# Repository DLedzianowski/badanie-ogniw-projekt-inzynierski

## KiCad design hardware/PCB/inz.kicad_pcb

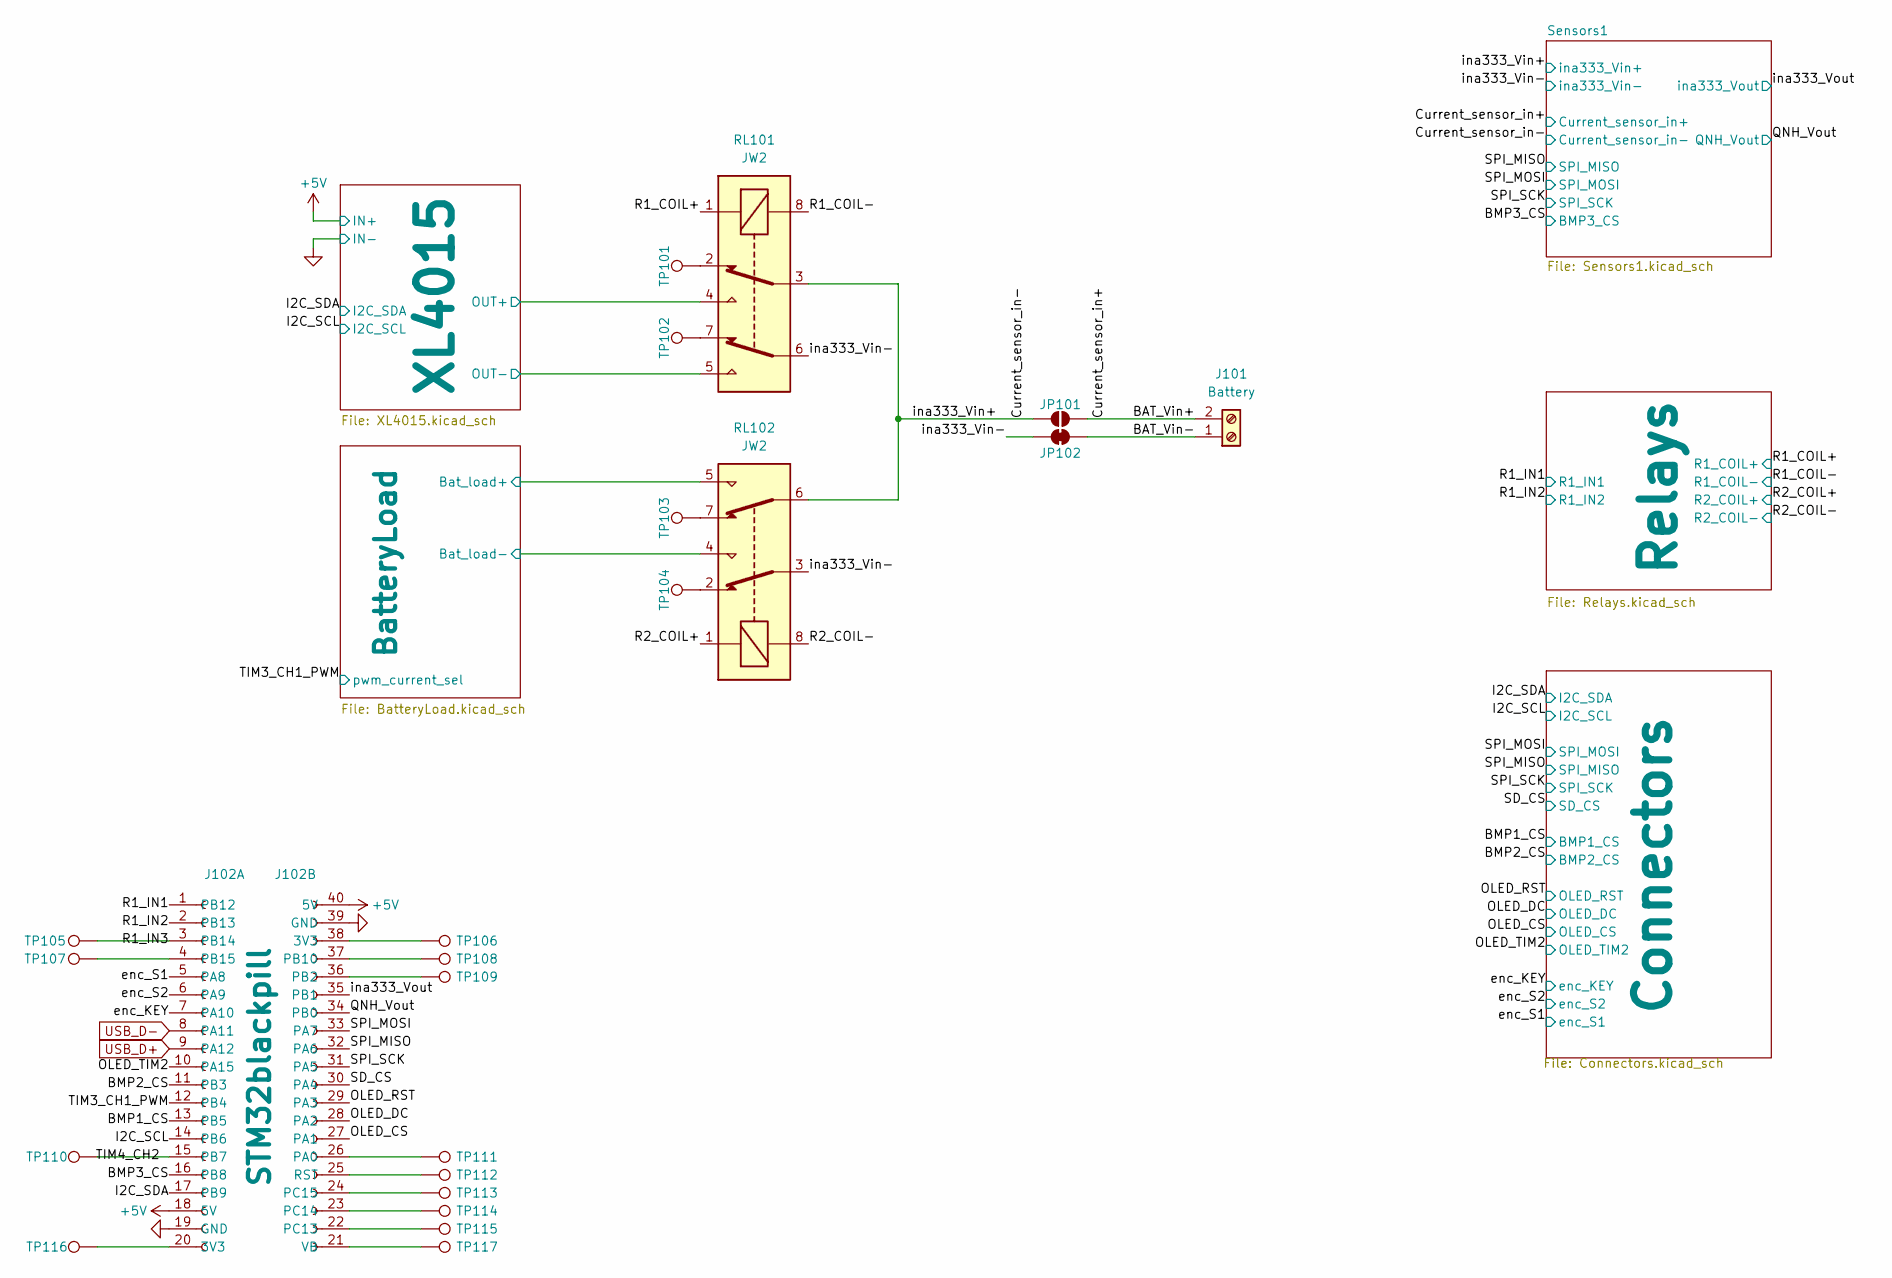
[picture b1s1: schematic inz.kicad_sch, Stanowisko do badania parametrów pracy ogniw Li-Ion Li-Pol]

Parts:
J101: Battery; TerminalBlock_Phoenix_MKDS-1,5-2_1x02_P5.00mm_Horizontal
J102: STM32blackpill; MFR Part ICSockets-40P; JLCPCB Part C2332
JP101: SolderJumper_2_Open; SolderJumper-2_P1.3mm_Open_TrianglePad1.0x1.5mm
JP102: Jumper_2_Bridged; PinHeader_1x02_P2.54mm_Vertical
RL101, RL102: JW2; Relay_DPDT_Panasonic_JW2; MFR Part JW2SN-DC5V
TP101, TP102, TP103, TP104, TP105, TP106, TP107, TP108, TP109, TP110, TP111, TP112, TP113, TP114, TP115, TP116, TP117: TestPoint; TestPoint_THTPad_D1.5mm_Drill0.7mm

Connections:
+5V: J102.18 (5V), J102.40 (5V), RL101.1, RL102.1; also elsewhere on the board
/BAT_Vin+: J101.2, JP101.1 (A); also elsewhere on the board
/BAT_Vin-: J101.1, JP102.2 (B)
/BMP1_CS: J102.13 (PB5); also elsewhere on the board
/BMP2_CS: J102.11 (PB3); also elsewhere on the board
/BMP3_CS: J102.16 (PB8); also elsewhere on the board
/BatteryLoad/Bat_load+: RL102.5; also elsewhere on the board
/Current_sensor_in-: JP101.2 (B), RL101.3, RL102.6; also elsewhere on the board
/I2C_SCL: J102.14 (PB6); also elsewhere on the board
/I2C_SDA: J102.17 (PB9); also elsewhere on the board
/OLED_CS: J102.27 (PA1); also elsewhere on the board
/OLED_DC: J102.28 (PA2); also elsewhere on the board
/OLED_RST: J102.29 (PA3); also elsewhere on the board
/OLED_TIM2: J102.10 (PA15); also elsewhere on the board
/QNH_Vout: J102.34 (PB0); also elsewhere on the board
/R1_COIL-: RL101.8; also elsewhere on the board
/R1_IN1: J102.1 (PB12); also elsewhere on the board
/R1_IN2: J102.2 (PB13); also elsewhere on the board
/R1_IN3: J102.3 (PB14), TP105.1
/R2_COIL-: RL102.8; also elsewhere on the board
/SD_CS: J102.30 (PA4); also elsewhere on the board
/SPI_MISO: J102.32 (PA6); also elsewhere on the board
/SPI_MOSI: J102.33 (PA7); also elsewhere on the board
/SPI_SCK: J102.31 (PA5); also elsewhere on the board
/TIM3_CH1_PWM: J102.12 (PB4); also elsewhere on the board
/TIM4_CH2: J102.15 (PB7), TP110.1
/XL4015/OUT+: RL101.4; also elsewhere on the board
/XL4015/OUT-: RL101.5; also elsewhere on the board
/enc_KEY: J102.7 (PA10); also elsewhere on the board
/enc_S1: J102.5 (PA8); also elsewhere on the board
/enc_S2: J102.6 (PA9); also elsewhere on the board
/ina333_Vin-: JP102.1 (A), RL101.6, RL102.3; also elsewhere on the board
/ina333_Vout: J102.35 (PB1); also elsewhere on the board
GND: J102.19 (GND), J102.39 (GND), RL102.4; also elsewhere on the board
unnamed: J102.20 (3V3), TP116.1
unnamed: J102.4 (PB15), TP107.1
unnamed: J102.38 (3V3), TP106.1
unnamed: J102.26 (PA0), TP111.1
unnamed: J102.36 (PB2), TP109.1
unnamed: J102.37 (PB10), TP108.1
unnamed: J102.22 (PC13), TP115.1
unnamed: J102.23 (PC14), TP114.1
unnamed: J102.24 (PC15), TP113.1
unnamed: J102.25 (RST), TP112.1
unnamed: J102.21 (VB), TP117.1
unnamed: RL101.2, TP101.1
unnamed: RL101.7, TP102.1
unnamed: RL102.2, TP104.1
unnamed: RL102.7, TP103.1
USB_D+: J102.9 (PA12); also elsewhere on the board
USB_D-: J102.8 (PA11); also elsewhere on the board

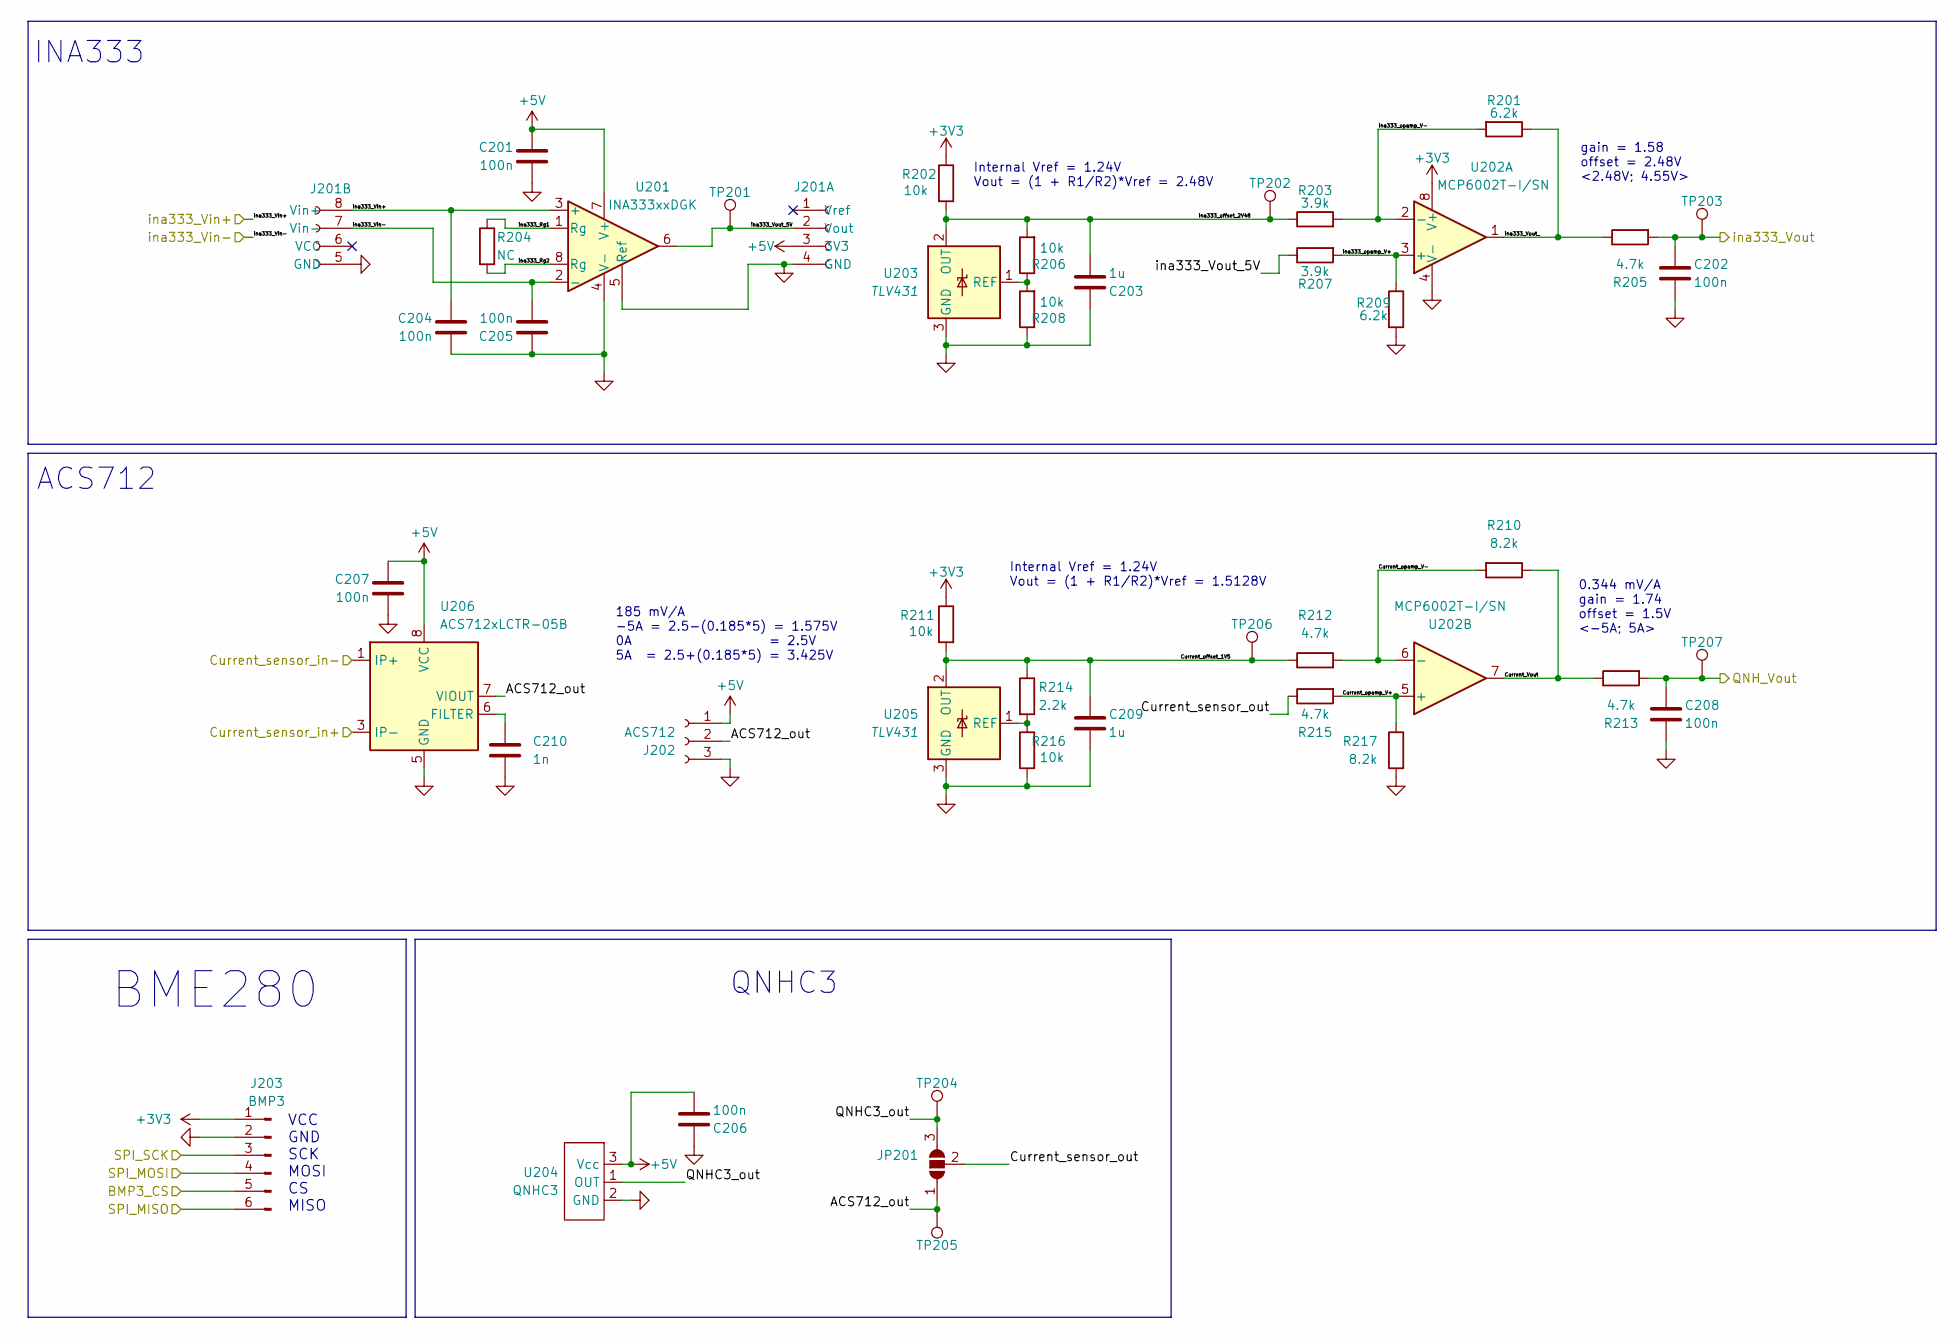
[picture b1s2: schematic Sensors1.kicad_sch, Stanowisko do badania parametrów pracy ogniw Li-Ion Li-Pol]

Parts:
C201, C202, C204, C205, C206, C207, C208: 100n; C_0805_2012Metric; MFR Part CL21B104KCFNNNE; JLCPCB Part C28233
C203, C209: 1u; C_0805_2012Metric; MFR Part CL21B105KBFNNNE; JLCPCB Part C28323
C210: 1n; C_0805_2012Metric; MFR Part CL21B102KBCNNNC; JLCPCB Part C46653
J201: ina333; board_ina333
J202: ACS712; PinHeader_1x03_P2.54mm_Vertical
J203: BMP3; PinHeader_1x06_P2.54mm_Vertical
JP201: SolderJumper_3_Open; SolderJumper-3_P2.0mm_Open_TrianglePad1.0x1.5mm_NumberLabels
R201, R209: 6.2k; R_0805_2012Metric; MFR Part 0805W8F6201T5E; JLCPCB Part C17767
R202, R206, R208, R211, R216: 10k; R_0805_2012Metric; MFR Part 0805W8F1002T5E; JLCPCB Part C17414
R203, R207: 3.9k; R_0805_2012Metric; MFR Part 0805W8F3901T5E; JLCPCB Part C17614
R204: NC; R_0805_2012Metric
R205, R212, R213, R215: 4.7k; R_0805_2012Metric; MFR Part 0805W8F4701T5E; JLCPCB Part C17673
R210, R217: 8.2k; R_0805_2012Metric; MFR Part 0805W8F8201T5E; JLCPCB Part C17828
R214: 2.2k; R_0805_2012Metric; MFR Part 0805W8F2201T5E; JLCPCB Part C17520
TP201, TP202, TP203, TP204, TP205, TP206, TP207: TestPoint; TestPoint_THTPad_D1.5mm_Drill0.7mm
U201: INA333xxDGK; VSSOP-8_3x3mm_P0.65mm; MFR Part INA333AIDGKT; JLCPCB Part C2057648
U202: MCP6002T-I/SN; SOIC-8_3.9x4.9mm_P1.27mm; MFR Part MCP6002T-I/SN; JLCPCB Part C7377
U203, U205: TLV431; SOT-23; MFR Part TLV431AIDBZR; JLCPCB Part C56765
U204: QNHC3
U206: ACS712xLCTR-05B; SOIC-8_3.9x4.9mm_P1.27mm; MFR Part ACS712ELCTR-05B-T; JLCPCB Part C44471

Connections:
+3V3: J203.1, R202.1, R211.1, U202.8 (V+); also elsewhere on the board
+5V: C201.1, C206.2, C207.1, J201.3 (3V3), J202.1, U201.7 (V+), U204.3 (Vcc), U206.8 (VCC); also elsewhere on the board
/BAT_Vin+: U206.3 (IP-), U206.4 (IP-); also elsewhere on the board
/BMP3_CS: J203.5; also elsewhere on the board
/Current_sensor_in-: C204.1, J201.8 (Vin+), U201.3 (+), U206.1 (IP+), U206.2 (IP+); also elsewhere on the board
/QNH_Vout: C208.1, R213.2, TP207.1; also elsewhere on the board
/SPI_MISO: J203.6; also elsewhere on the board
/SPI_MOSI: J203.4; also elsewhere on the board
/SPI_SCK: J203.3; also elsewhere on the board
/Sensors1/ACS712_out: J202.2, JP201.1 (A), TP205.1, U206.7 (VIOUT)
/Sensors1/Current_Vout: R210.1, R213.1, U202.7
/Sensors1/Current_offset_1V5: C209.1, R211.2, R212.1, R214.1, TP206.1, U205.2 (OUT)
/Sensors1/Current_opamp_V+: R215.2, R217.1, U202.5 (+)
/Sensors1/Current_opamp_V-: R210.2, R212.2, U202.6 (-)
/Sensors1/Current_sensor_out: JP201.2 (C), R215.1
/Sensors1/QNHC3_out: JP201.3 (B), TP204.1, U204.1 (OUT)
/Sensors1/ina333_Rg1: R204.1, U201.1 (Rg)
/Sensors1/ina333_Rg2: R204.2, U201.8 (Rg)
/Sensors1/ina333_Vout_: R201.1, R205.1, U202.1
/Sensors1/ina333_Vout_5V: J201.2 (Vout), R207.1, TP201.1, U201.6
/Sensors1/ina333_offset_2V48: C203.2, R202.2, R203.1, R206.2, TP202.1, U203.2 (OUT)
/Sensors1/ina333_opamp_V+: R207.2, R209.1, U202.3 (+)
/Sensors1/ina333_opamp_V-: R201.2, R203.2, U202.2 (-)
/ina333_Vin-: C205.2, J201.7 (Vin-), U201.2 (-); also elsewhere on the board
/ina333_Vout: C202.1, R205.2, TP203.1; also elsewhere on the board
GND: C201.2, C202.2, C203.1, C204.2, C205.1, C206.1, C207.2, C208.2, C209.2, C210.2, J201.4 (GND), J201.5 (GND), J202.3, J203.2, R208.1, R209.2, R216.2, R217.2, U201.4 (V-), U201.5 (Ref), U202.4 (V-), U203.3 (GND), U204.2 (GND), U205.3 (GND), U206.5 (GND); also elsewhere on the board
unnamed: R206.1, R208.2, U203.1 (REF)
unnamed: R214.2, R216.1, U205.1 (REF)
unnamed: C210.1, U206.6 (FILTER)

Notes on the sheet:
BME280
185 mV/A -5A = 2.5-(0.185*5) = 1.575V 0A = 2.5V 5A = 2.5+(0.185*5) = 3.425V
Internal Vref = 1.24V Vout = (1 + R1/R2)*Vref = 2.48V
gain = 1.58 offset = 2.48V <2.48V; 4.55V>
VCC GND SCK MOSI CS MISO
QNHC3
INA333
ACS712
Internal Vref = 1.24V Vout = (1 + R1/R2)*Vref = 1.5128V
0.344 mV/A gain = 1.74 offset = 1.5V <-5A; 5A>

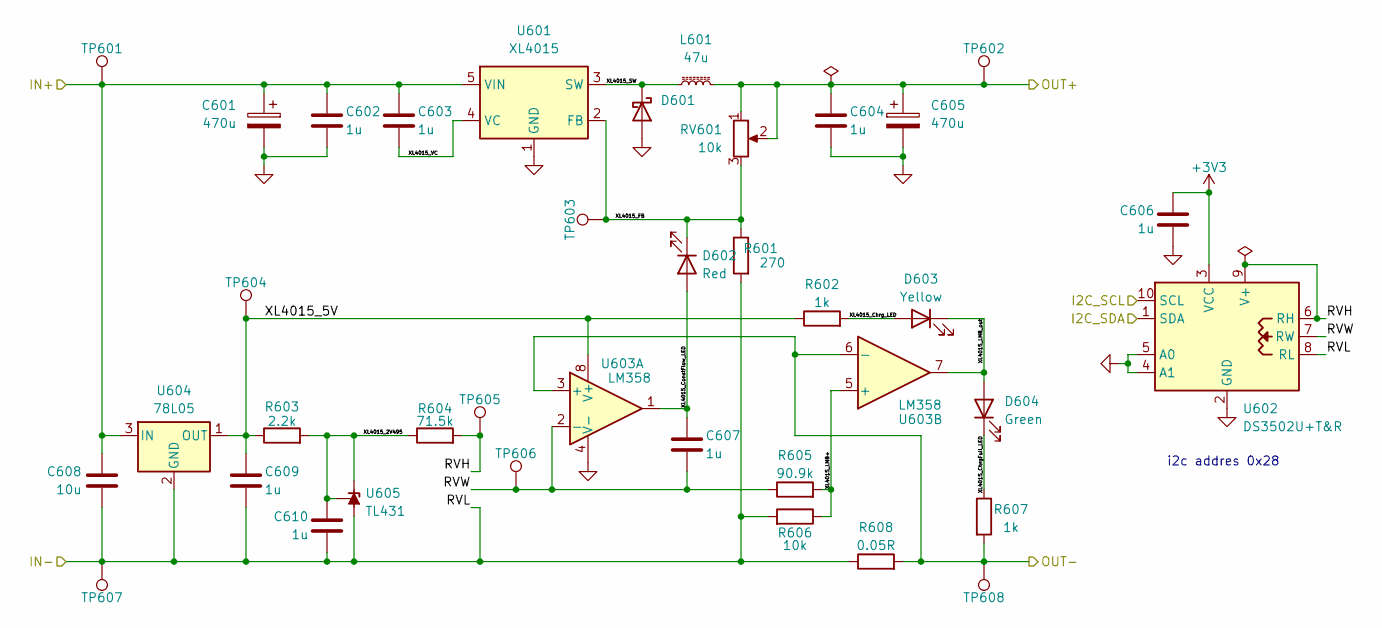
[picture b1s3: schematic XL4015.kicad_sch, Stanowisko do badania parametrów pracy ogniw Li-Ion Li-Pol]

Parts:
C601, C605: 470u; C_Elec_10x10.2; MFR Part RVT1E471M1010; JLCPCB Part C3351
C602, C603, C604, C606, C607, C609, C610: 1u; C_0805_2012Metric; MFR Part CL21B105KBFNNNE; JLCPCB Part C28323
C608: 10u; C_1206_3216Metric; MFR Part CL31A106KOHNNNE; JLCPCB Part C1849
D601: MBRD1045; D_SMA; MFR Part C22452; JLCPCB Part C22452
D602: Red; LED_0805_2012Metric; MFR Part NCD0805R1; JLCPCB Part C84256
D603: Yellow; LED_0805_2012Metric; MFR Part KT-0805Y; JLCPCB Part C2296
D604: Green; LED_0805_2012Metric; MFR Part KT-0805G; JLCPCB Part C2297
L601: 47u; L_Toroid_Vertical_L16.0mm_W8.0mm_P7.62mm; MFR Part XR050125TS470MVL8; JLCPCB Part C18213949
R601: 270; R_0805_2012Metric; MFR Part 0805W8F2700T5E; JLCPCB Part C17590
R602, R607: 1k; R_0805_2012Metric; MFR Part 0805W8F1001T5E; JLCPCB Part C17513
R603: 2.2k; R_0805_2012Metric; MFR Part 0805W8F2201T5E; JLCPCB Part C17520
R604: 71.5k; R_0805_2012Metric; MFR Part 0805W8F7152T5E; JLCPCB Part C17811
R605: 90.9k; R_0805_2012Metric; MFR Part 0805W8F9092T5E; JLCPCB Part C17860
R606: 10k; R_0805_2012Metric; MFR Part 0805W8F1002T5E; JLCPCB Part C17414
R608: 0.05R; R_2512_6332Metric; MFR Part 25121WF500MT4E; JLCPCB Part C127698
RV601: 10k; Potentiometer_Bourns_3299W_Vertical
TP601, TP602, TP603, TP604, TP605, TP606, TP607, TP608: TestPoint; TestPoint_THTPad_D1.5mm_Drill0.7mm
U601: XL4015; TO-263-5_TabPin3; MFR Part XL4015E1; JLCPCB Part C51661
U602: DS3502U+T&R; TSSOP-10_3x3mm_P0.5mm; MFR Part DS3502U+T&R; JLCPCB Part C2649363
U603: LM358; SOIC-8_3.9x4.9mm_P1.27mm; MFR Part LM358DR2G; JLCPCB Part C7950
U604: 78L05; SOT-89-3; MFR Part 78L05G-AB3-R; JLCPCB Part C71136
U605: TL431; SOT-23-3; MFR Part TL431BQDBZR; JLCPCB Part C190245

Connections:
+3V3: C606.1, U602.3 (VCC); also elsewhere on the board
+5V: C601.1, C602.1, C603.1, C608.1, TP601.1, U601.5 (VIN), U604.3 (IN); also elsewhere on the board
/I2C_SCL: U602.10 (SCL); also elsewhere on the board
/I2C_SDA: U602.1 (SDA); also elsewhere on the board
/XL4015/OUT+: C604.1, C605.1, L601.2, RV601.1, RV601.2, TP602.1; also elsewhere on the board
/XL4015/OUT-: R607.2, R608.2, TP608.1, U603.3 (+), U603.6 (-); also elsewhere on the board
/XL4015/RVH: R604.2, TP605.1, U602.6 (RH), U602.9 (V+)
/XL4015/RVW: C607.2, R605.1, TP606.1, U602.7 (RW), U603.2 (-)
/XL4015/XL4015_2V495: C610.1, R603.2, R604.1, U605.1 (K), U605.2 (REF)
/XL4015/XL4015_5V: C609.1, R602.1, R603.1, TP604.1, U603.8 (V+), U604.1 (OUT)
/XL4015/XL4015_ChrgFull_LED: D604.1 (K), R607.1
/XL4015/XL4015_Chrg_LED: D603.2 (A), R602.2
/XL4015/XL4015_ConstFlow_LED: C607.1, D602.2 (A), U603.1
/XL4015/XL4015_FB: D602.1 (K), R601.1, RV601.3, TP603.1, U601.2 (FB)
/XL4015/XL4015_LMB+: R605.2, R606.1, U603.5 (+)
/XL4015/XL4015_LMB_out: D603.1 (K), D604.2 (A), U603.7
/XL4015/XL4015_SW: D601.1 (K), L601.1, U601.3 (SW)
/XL4015/XL4015_VC: C603.2, U601.4 (VC)
GND: C601.2, C602.2, C604.2, C605.2, C606.2, C608.2, C609.2, C610.2, D601.2 (A), R601.2, R606.2, R608.1, TP607.1, U601.1 (GND), U602.2 (GND), U602.4 (A1), U602.5 (A0), U602.8 (RL), U603.4 (V-), U604.2 (GND), U605.3 (A); also elsewhere on the board

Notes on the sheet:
i2c addres 0x28

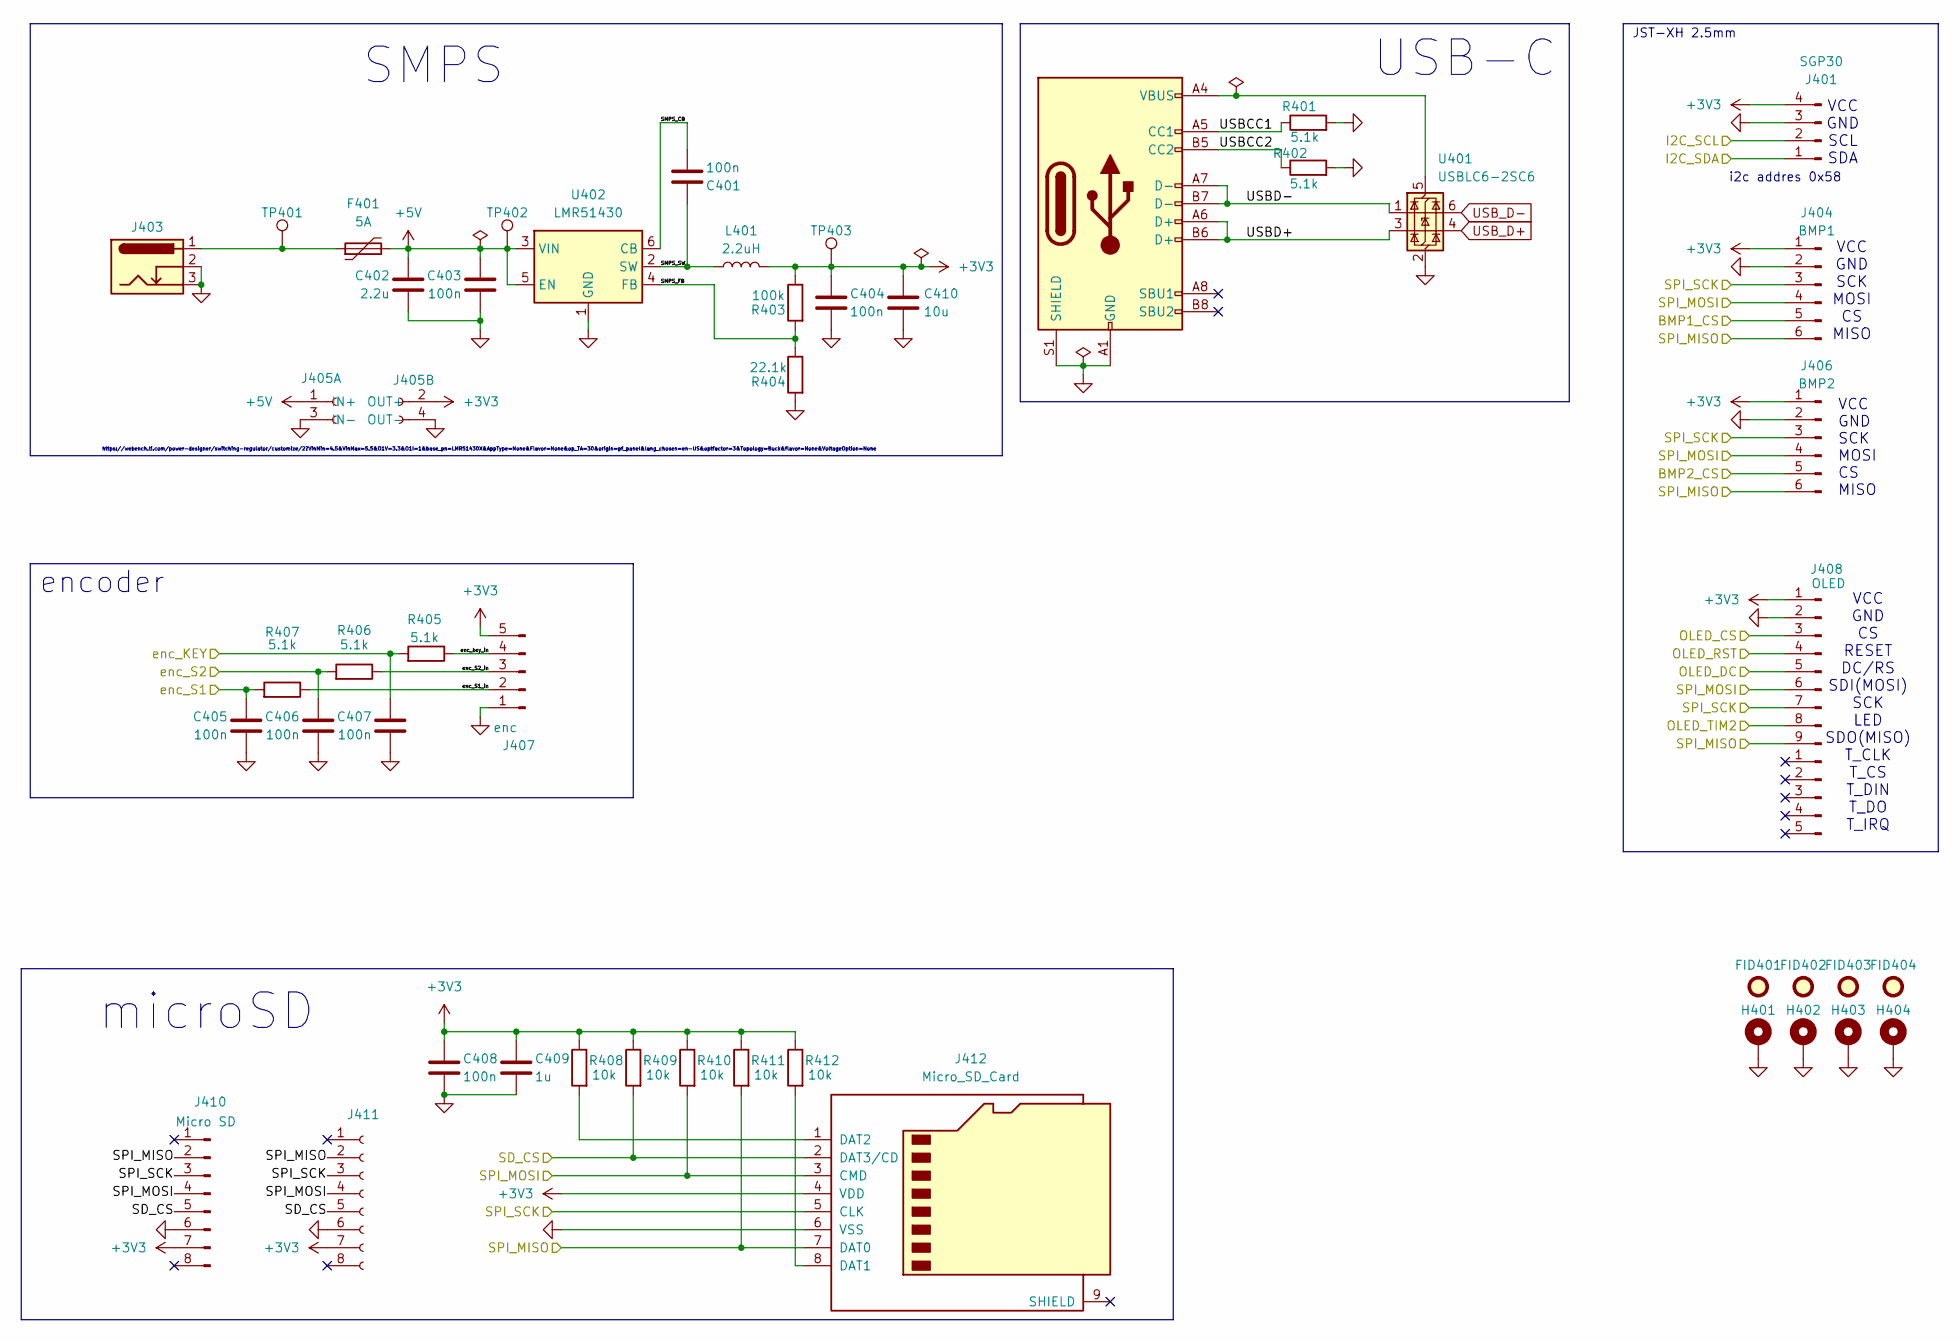
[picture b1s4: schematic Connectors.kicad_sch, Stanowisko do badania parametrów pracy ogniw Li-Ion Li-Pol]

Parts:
C401, C405, C406, C407, C408: 100n; C_0805_2012Metric; MFR Part CL21B104KCFNNNE; JLCPCB Part C28233
C402: 2.2u; C_0805_2012Metric; MFR Part CL21A225KBQNNNE; JLCPCB Part C377773
C403, C404: 100n; C_0805_2012Metric; MFR Part CL21B104KBCNNNC; JLCPCB Part C1711
C409: 1u; C_0805_2012Metric; MFR Part CL21B105KBFNNNE; JLCPCB Part C28323
C410: 10u; C_1206_3216Metric; MFR Part CL31A106KOHNNNE; JLCPCB Part C1849
F401: 5A; Fuseholder_Clip-5x20mm
FID401, FID402, FID403, FID404: Fiducial; Fiducial_1mm_Mask2mm
H401, H402, H403, H404: MountingHole_Pad; MountingHole_3.2mm_M3_Pad
J401: SGP30; JST_XH_B4B-XH-A_1x04_P2.50mm_Vertical; MFR Part B4B-XH-A(LF)(SN); JLCPCB Part C144395
J402: USBC; USB_C_16P; MFR Part TYPE-C-31-M-48; JLCPCB Part C47817612
J403: 5V; BarrelJack_GCT_DCJ200-10-A_Horizontal; MFR Part DC-005H-D020; JLCPCB Part C5155559
J404: BMP1; JST_XH_B6B-XH-A_1x06_P2.50mm_Vertical; MFR Part B6B-XH-A(LF)(SN); JLCPCB Part C144397
J405: board_step-down
J406: BMP2; JST_XH_B6B-XH-A_1x06_P2.50mm_Vertical; MFR Part B6B-XH-A(LF)(SN); JLCPCB Part C144397
J407: enc; JST_XH_B5B-XH-A_1x05_P2.50mm_Vertical; MFR Part B5B-XH-A(LF)(SN); JLCPCB Part C157991
J408: OLED; JST_XH_B9B-XH-A_1x09_P2.50mm_Vertical; MFR Part B9B-XH-A(LF)(SN); JLCPCB Part C157966
J409: Conn_01x05_Pin; JST_XH_B5B-XH-A_1x05_P2.50mm_Vertical
J410: Micro SD; board_smd_sd
J411: Micro SD2; PinHeader_1x08_P2.54mm_Vertical
J412: Micro_SD_Card; microSD; MFR Part TF-021B-H265; JLCPCB Part C498185
L401: 2.2uH; SMD,10.4x10.3mm; MFR Part SXN(Shun Xiang Nuo Elec); JLCPCB Part C10164
R401, R402, R405, R406, R407: 5.1k; R_0805_2012Metric; MFR Part 0805W8F5101T5E; JLCPCB Part C27834
R403: 100k; R_0805_2012Metric; MFR Part 0805W8F1003T5E; JLCPCB Part C149504
R404: 22.1k; R_0805_2012Metric; MFR Part 0805W8F2212T5E; JLCPCB Part C17552
R408, R409, R410, R411, R412: 10k; R_0805_2012Metric; MFR Part 0805W8F1002T5E; JLCPCB Part C17414
TP401, TP402, TP403: TestPoint; TestPoint_THTPad_D1.5mm_Drill0.7mm
U401: USBLC6-2SC6; SOT-23-6; MFR Part USBLC6-2SC6; JLCPCB Part C7519
U402: LMR51430; SOT-23-6; MFR Part LMR51430XDDCR; JLCPCB Part C5185863

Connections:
+3V3: C404.1, C408.1, C409.1, C410.1, J401.4, J404.1, J405.2 (OUT+), J406.1, J407.5, J408.1, J410.7, J411.7, J412.4 (VDD), L401.2, R403.1, R408.1, R409.1, R410.1, R411.1, R412.1, TP403.1; also elsewhere on the board
+5V: C402.1, C403.1, F401.2, J405.1 (IN+), TP402.1, U402.3 (VIN), U402.5 (EN); also elsewhere on the board
/BMP1_CS: J404.5; also elsewhere on the board
/BMP2_CS: J406.5; also elsewhere on the board
/Connectors/SMPS_CB: C401.2, U402.6 (CB)
/Connectors/SMPS_FB: R403.2, R404.1, U402.4 (FB)
/Connectors/SMPS_SW: C401.1, L401.1, U402.2 (SW)
/Connectors/USBCC1: J402.A5 (CC1), R401.1
/Connectors/USBCC2: J402.B5 (CC2), R402.1
/Connectors/USBD+: J402.A6 (D+), J402.B6 (D+), U401.3 (I/O2)
/Connectors/USBD-: J402.A7 (D-), J402.B7 (D-), U401.1 (I/O1)
/Connectors/enc_S1_in: J407.2, R407.1
/Connectors/enc_S2_in: J407.3, R406.1
/Connectors/enc_key_in: J407.4, R405.1
/I2C_SCL: J401.2; also elsewhere on the board
/I2C_SDA: J401.1; also elsewhere on the board
/OLED_CS: J408.3; also elsewhere on the board
/OLED_DC: J408.5; also elsewhere on the board
/OLED_RST: J408.4; also elsewhere on the board
/OLED_TIM2: J408.8; also elsewhere on the board
/SD_CS: J410.5, J411.5, J412.2 (DAT3/CD), R409.2; also elsewhere on the board
/SPI_MISO: J404.6, J406.6, J408.9, J410.2, J411.2, J412.7 (DAT0), R411.2; also elsewhere on the board
/SPI_MOSI: J404.4, J406.4, J408.6, J410.4, J411.4, J412.3 (CMD), R410.2; also elsewhere on the board
/SPI_SCK: J404.3, J406.3, J408.7, J410.3, J411.3, J412.5 (CLK); also elsewhere on the board
/enc_KEY: C407.1, R405.2; also elsewhere on the board
/enc_S1: C405.1, R407.2; also elsewhere on the board
/enc_S2: C406.1, R406.2; also elsewhere on the board
GND: C402.2, C403.2, C404.2, C405.2, C406.2, C407.2, C408.2, C409.2, C410.2, H401.1, H402.1, H403.1, H404.1, J401.3, J402.A1 (GND), J402.A12 (GND), J402.B1 (GND), J402.B12 (GND), J402.S1 (SHIELD), J403.2, J403.3, J404.2, J405.3 (IN-), J405.4 (OUT-), J406.2, J407.1, J408.2, J410.6, J411.6, J412.6 (VSS), R401.2, R402.2, R404.2, U401.2 (GND), U402.1 (GND); also elsewhere on the board
unnamed: F401.1, J403.1, TP401.1
unnamed: J412.8 (DAT1), R412.2
unnamed: J412.1 (DAT2), R408.2
unnamed: J402.A4 (VBUS), J402.A9 (VBUS), J402.B4 (VBUS), J402.B9 (VBUS), U401.5 (VBUS)
USB_D+: U401.4 (I/O2); also elsewhere on the board
USB_D-: U401.6 (I/O1); also elsewhere on the board

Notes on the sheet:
VCC GND SCL SDA
SMPS
microSD
VCC GND SCK MOSI CS MISO
i2c addres 0x58
USB-C
encoder
https://webench.ti.com/power-designer/switching-regulator/customize/2?VinMin=4.5&VinMax=5.5&O1V=3.3&O1I=1&base_pn=LMR51430X&AppType=None&Flavor=None&op_TA=30&origin=pf_panel&lang_chosen=en-US&optfactor=3&Topology=Buck&flavor=None&VoltageOption=None
JST-XH 2.5mm
VCC GND CS RESET DC/RS SDI(MOSI) SCK LED SDO(MISO) T_CLK T_CS T_DIN T_DO T_IRQ
VCC GND SCK MOSI CS MISO

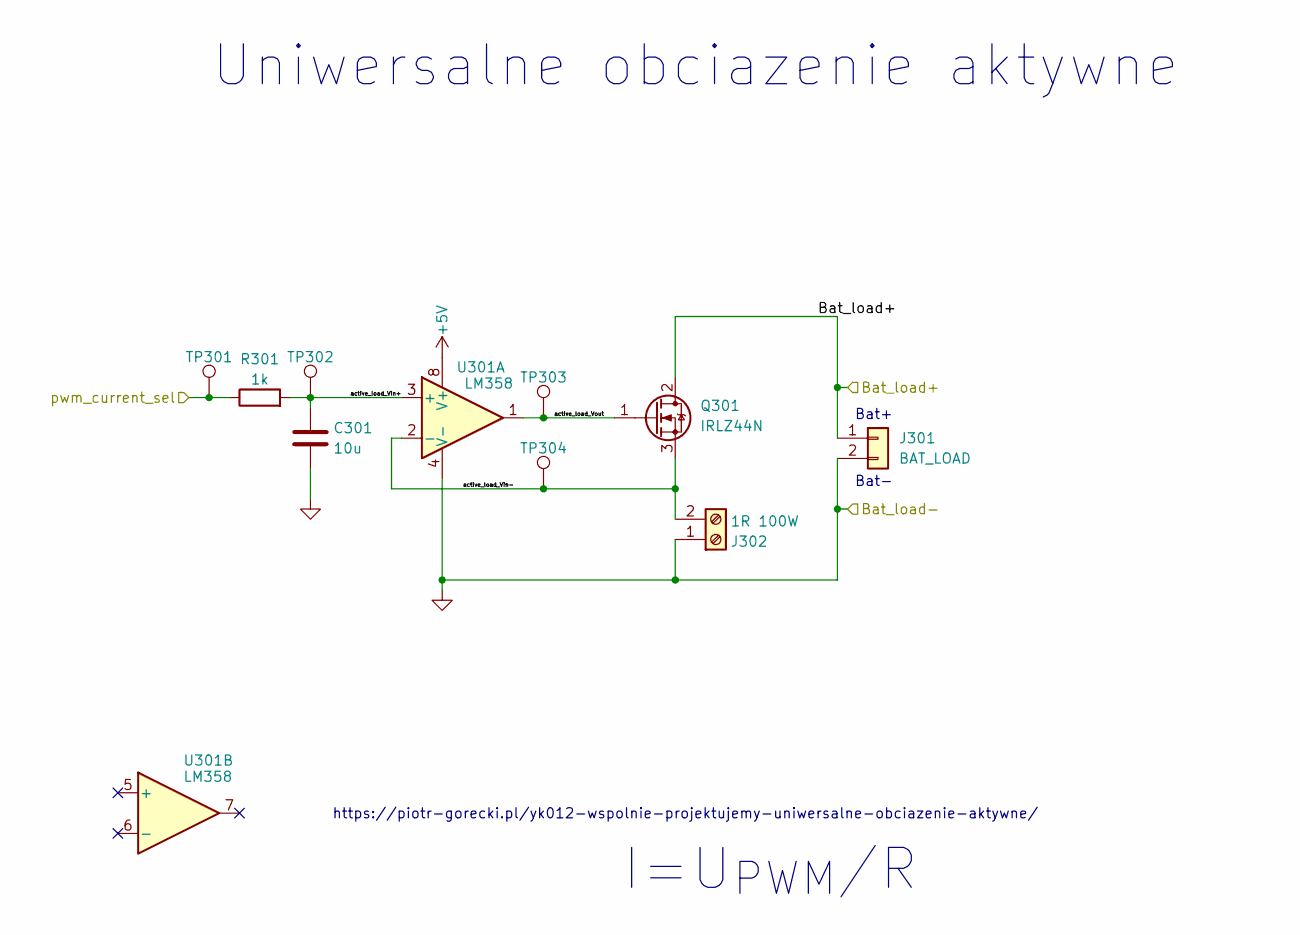
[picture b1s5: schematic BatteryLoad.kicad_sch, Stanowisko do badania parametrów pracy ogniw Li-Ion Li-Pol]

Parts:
C301: 10u; C_1206_3216Metric; MFR Part CL31A106KOHNNNE; JLCPCB Part C1849
J301: BAT_LOAD; TerminalBlock_MaiXu_MX126-5.0-02P_1x02_P5.00mm
J302: 1R 100W; TerminalBlock_Phoenix_MKDS-1,5-2_1x02_P5.00mm_Horizontal
Q301: IRLZ44N; TO-220-3_Vertical; MFR Part IRLZ44NPBF; JLCPCB Part C38774
R301: 1k; R_0805_2012Metric; MFR Part 0805W8F1001T5E; JLCPCB Part C17513
TP301, TP302, TP303, TP304: TestPoint; TestPoint_THTPad_D1.5mm_Drill0.7mm
U301: LM358; SOIC-8_3.9x4.9mm_P1.27mm; MFR Part LM358DR2G; JLCPCB Part C7950

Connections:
+5V: U301.8 (V+); also elsewhere on the board
/BatteryLoad/Bat_load+: J301.1, Q301.2 (D); also elsewhere on the board
/BatteryLoad/active_load_Vin+: C301.1, R301.2, TP302.1, U301.3 (+)
/BatteryLoad/active_load_Vin-: J302.2, Q301.3 (S), TP304.1, U301.2 (-)
/BatteryLoad/active_load_Vout: Q301.1 (G), TP303.1, U301.1
/TIM3_CH1_PWM: R301.1, TP301.1; also elsewhere on the board
GND: C301.2, J301.2, J302.1, U301.4 (V-); also elsewhere on the board

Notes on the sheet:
Uniwersalne obciazenie aktywne
Bat-
I=U_{PWM}/R
https://piotr-gorecki.pl/yk012-wspolnie-projektujemy-uniwersalne-obciazenie-aktywne/
Bat+

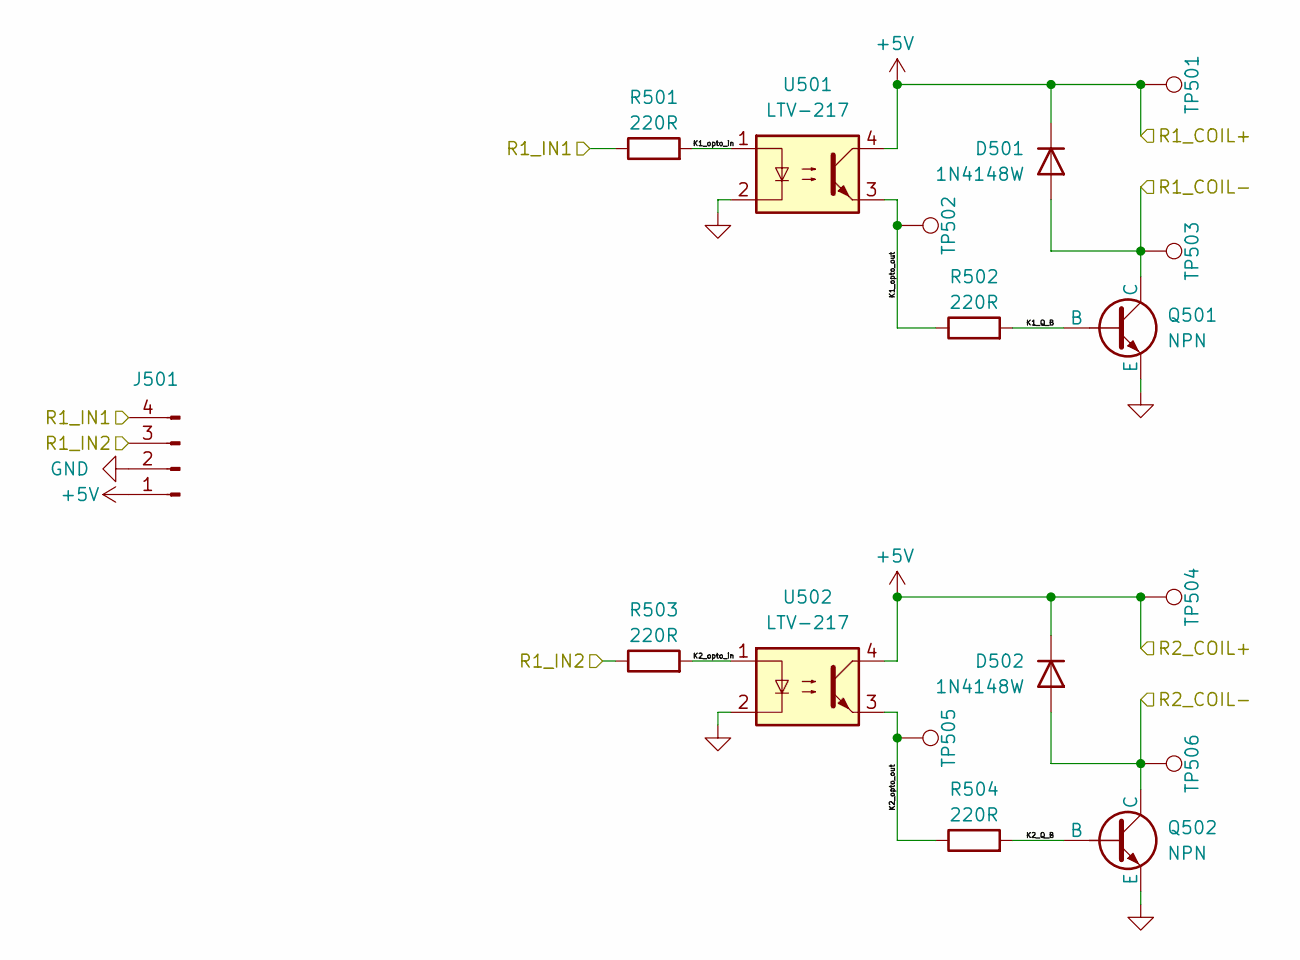
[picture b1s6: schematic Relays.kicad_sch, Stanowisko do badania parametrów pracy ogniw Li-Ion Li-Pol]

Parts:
D501, D502: 1N4148W; D_SOD-123; MFR Part 1N4148W; JLCPCB Part C81598
J501: Conn_01x04_Pin; PinHeader_1x04_P2.54mm_Vertical
Q501, Q502: NPN; SOT-23; MFR Part MMBT3904(RANGE:100-300); JLCPCB Part C20526
R501, R502, R503, R504: 220R; R_0805_2012Metric; MFR Part 0805W8F2200T5E; JLCPCB Part C17557
TP501, TP502, TP503, TP504, TP505, TP506: TestPoint; TestPoint_THTPad_D1.5mm_Drill0.7mm
U501, U502: LTV-217; SOP-4_4.4x2.6mm_P1.27mm; MFR Part LTV-217-B-G; JLCPCB Part C115450

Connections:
+5V: D501.1 (K), D502.1 (K), J501.1, TP501.1, TP504.1, U501.4, U502.4; also elsewhere on the board
/R1_COIL-: D501.2 (A), Q501.1 (C), TP503.1; also elsewhere on the board
/R1_IN1: J501.4, R501.1; also elsewhere on the board
/R1_IN2: J501.3, R503.1; also elsewhere on the board
/R2_COIL-: D502.2 (A), Q502.1 (C), TP506.1; also elsewhere on the board
/Relays/K1_Q_B: Q501.2 (B), R502.2
/Relays/K1_opto_in: R501.2, U501.1
/Relays/K1_opto_out: R502.1, TP502.1, U501.3
/Relays/K2_Q_B: Q502.2 (B), R504.2
/Relays/K2_opto_in: R503.2, U502.1
/Relays/K2_opto_out: R504.1, TP505.1, U502.3
GND: J501.2, Q501.3 (E), Q502.3 (E), U501.2, U502.2; also elsewhere on the board
